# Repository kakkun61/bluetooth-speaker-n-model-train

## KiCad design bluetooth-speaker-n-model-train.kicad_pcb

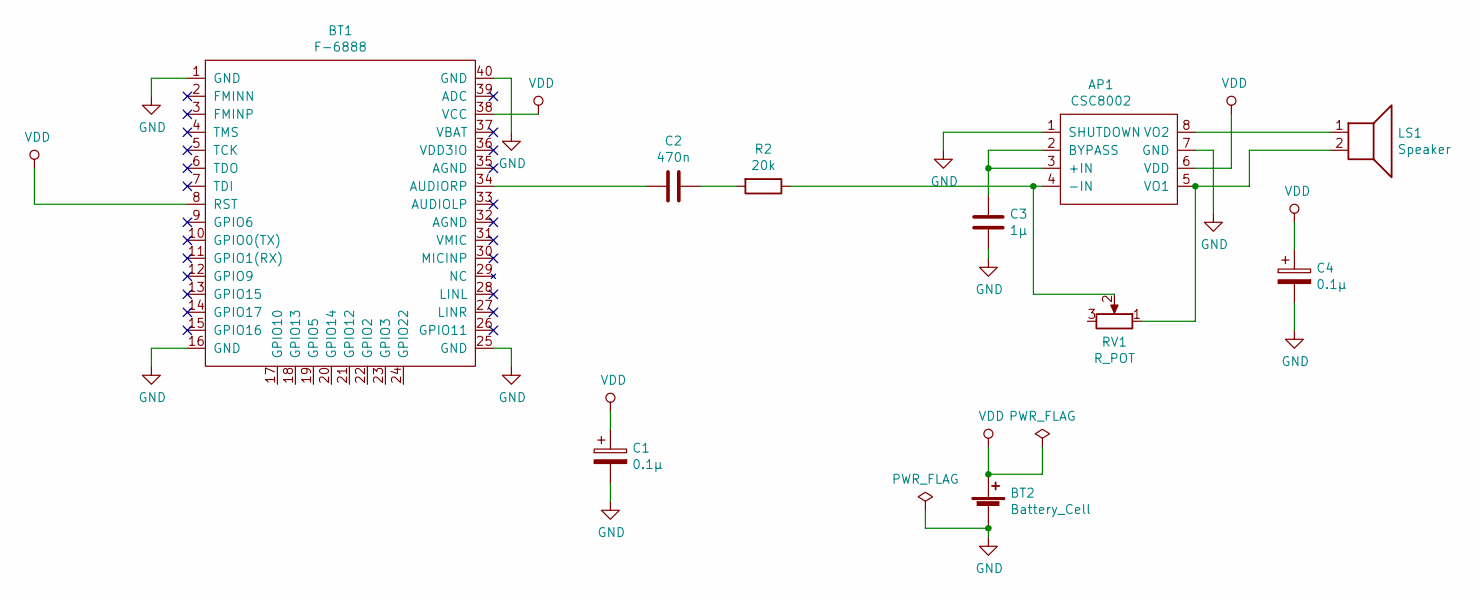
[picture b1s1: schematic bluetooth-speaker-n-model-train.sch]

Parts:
AP1: CSC8002; SOIC-8_3.9x4.9mm_P1.27mm
BT1: F-6888
BT2: Battery_Cell; TestPoint_2Pads_Pitch2.54mm_Drill0.8mm
C1, C4: 0.1μ; C_1206_3216Metric
C2: 470n; C_1206_3216Metric
C3: 1μ; C_1206_3216Metric
LS1: Speaker; TestPoint_2Pads_Pitch2.54mm_Drill0.8mm
R2: 20k; C_1206_3216Metric
RV1: R_POT; Potentiometers_Tocos_GF063P

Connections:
GND: AP1.1 (SHUTDOWN), AP1.7 (GND), BT1.1 (GND), BT1.16 (GND), BT1.25 (GND), BT1.40 (GND), BT2.2 (-), C1.2, C3.2, C4.2
unnamed: AP1.2 (BYPASS), AP1.3 (+IN), C3.1
unnamed: AP1.4 (-IN), R2.1, RV1.2
unnamed: AP1.5 (VO1), LS1.2, RV1.1
unnamed: AP1.8 (VO2), LS1.1
unnamed: BT1.34 (AUDIORP), C2.2
unnamed: C2.1, R2.2
VDD: AP1.6 (VDD), BT1.8 (RST), BT1.38 (VCC), BT2.1 (+), C1.1, C4.1

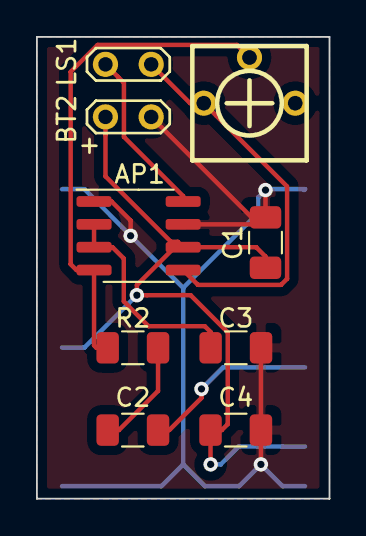
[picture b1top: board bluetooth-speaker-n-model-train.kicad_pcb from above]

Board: 2 copper layers, 16.3 x 25.7 mm, 10 parts (1 on the bottom side), 8 nets.

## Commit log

2022-03-30 init
